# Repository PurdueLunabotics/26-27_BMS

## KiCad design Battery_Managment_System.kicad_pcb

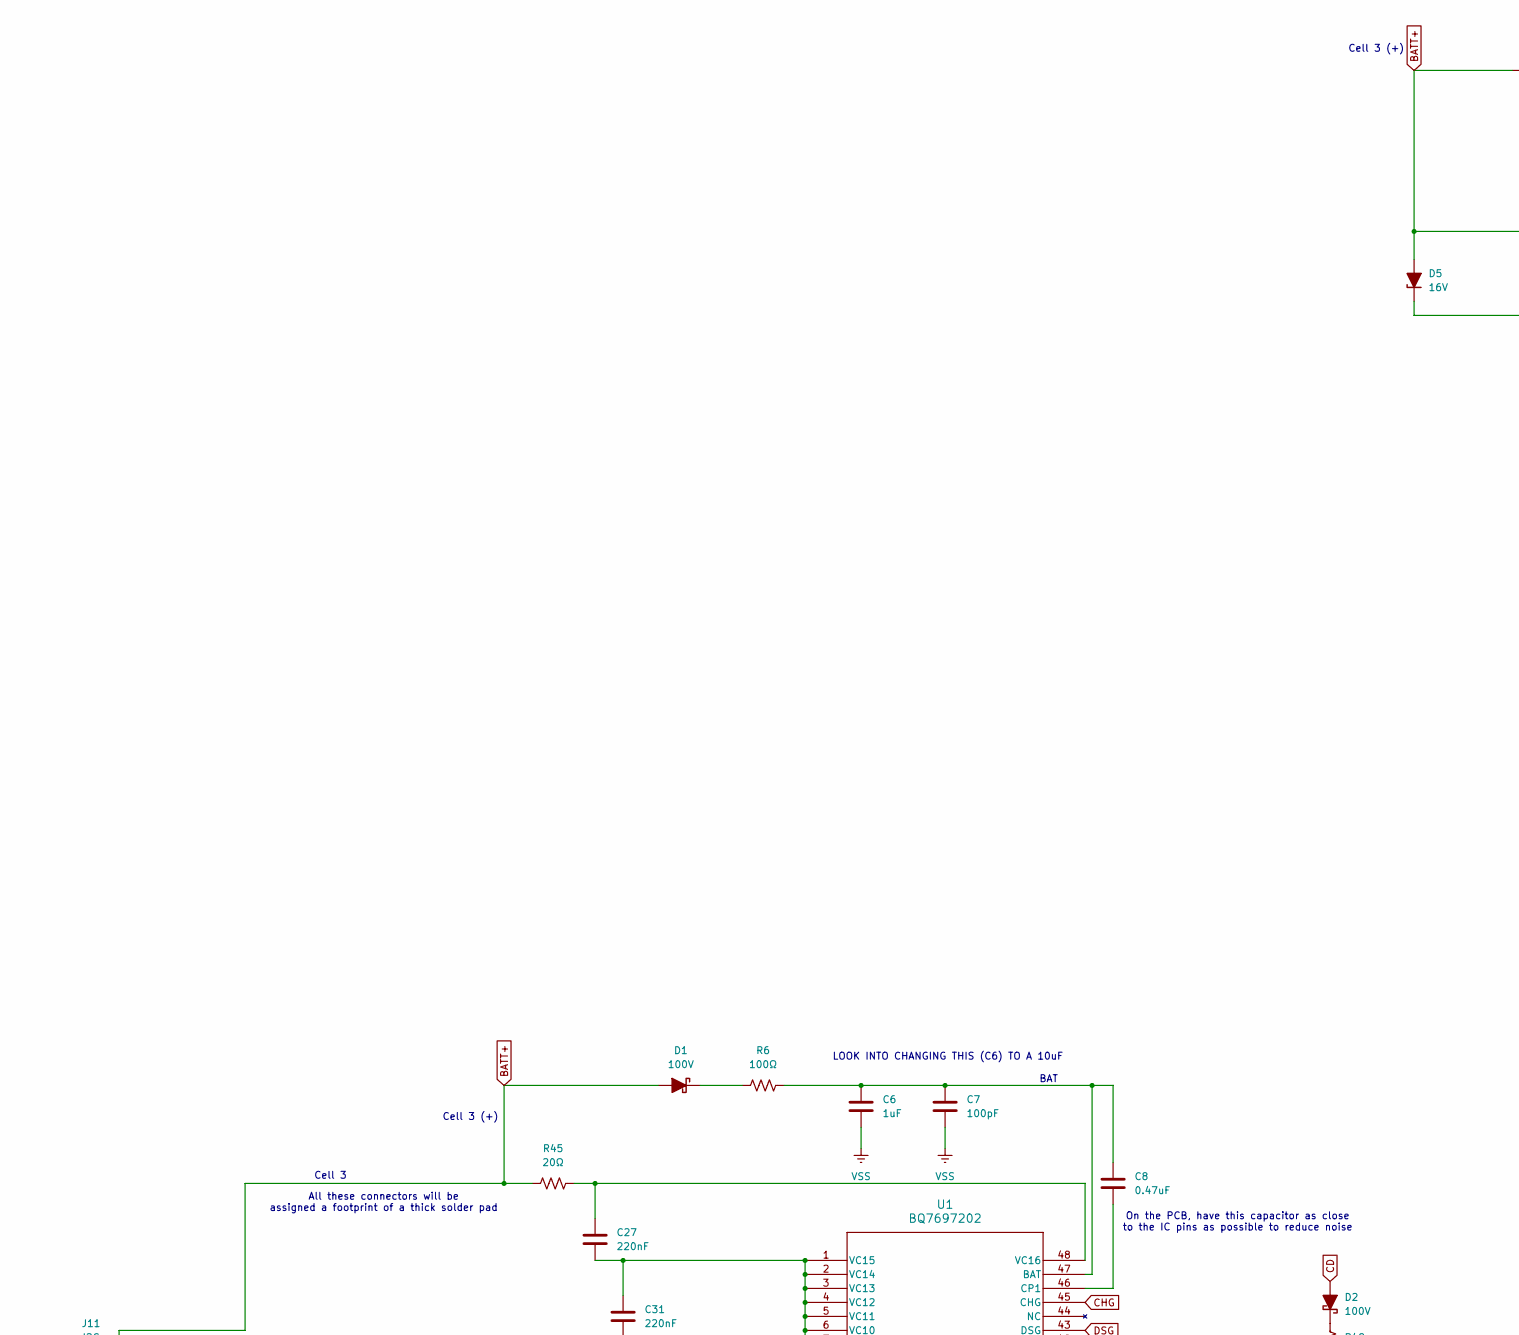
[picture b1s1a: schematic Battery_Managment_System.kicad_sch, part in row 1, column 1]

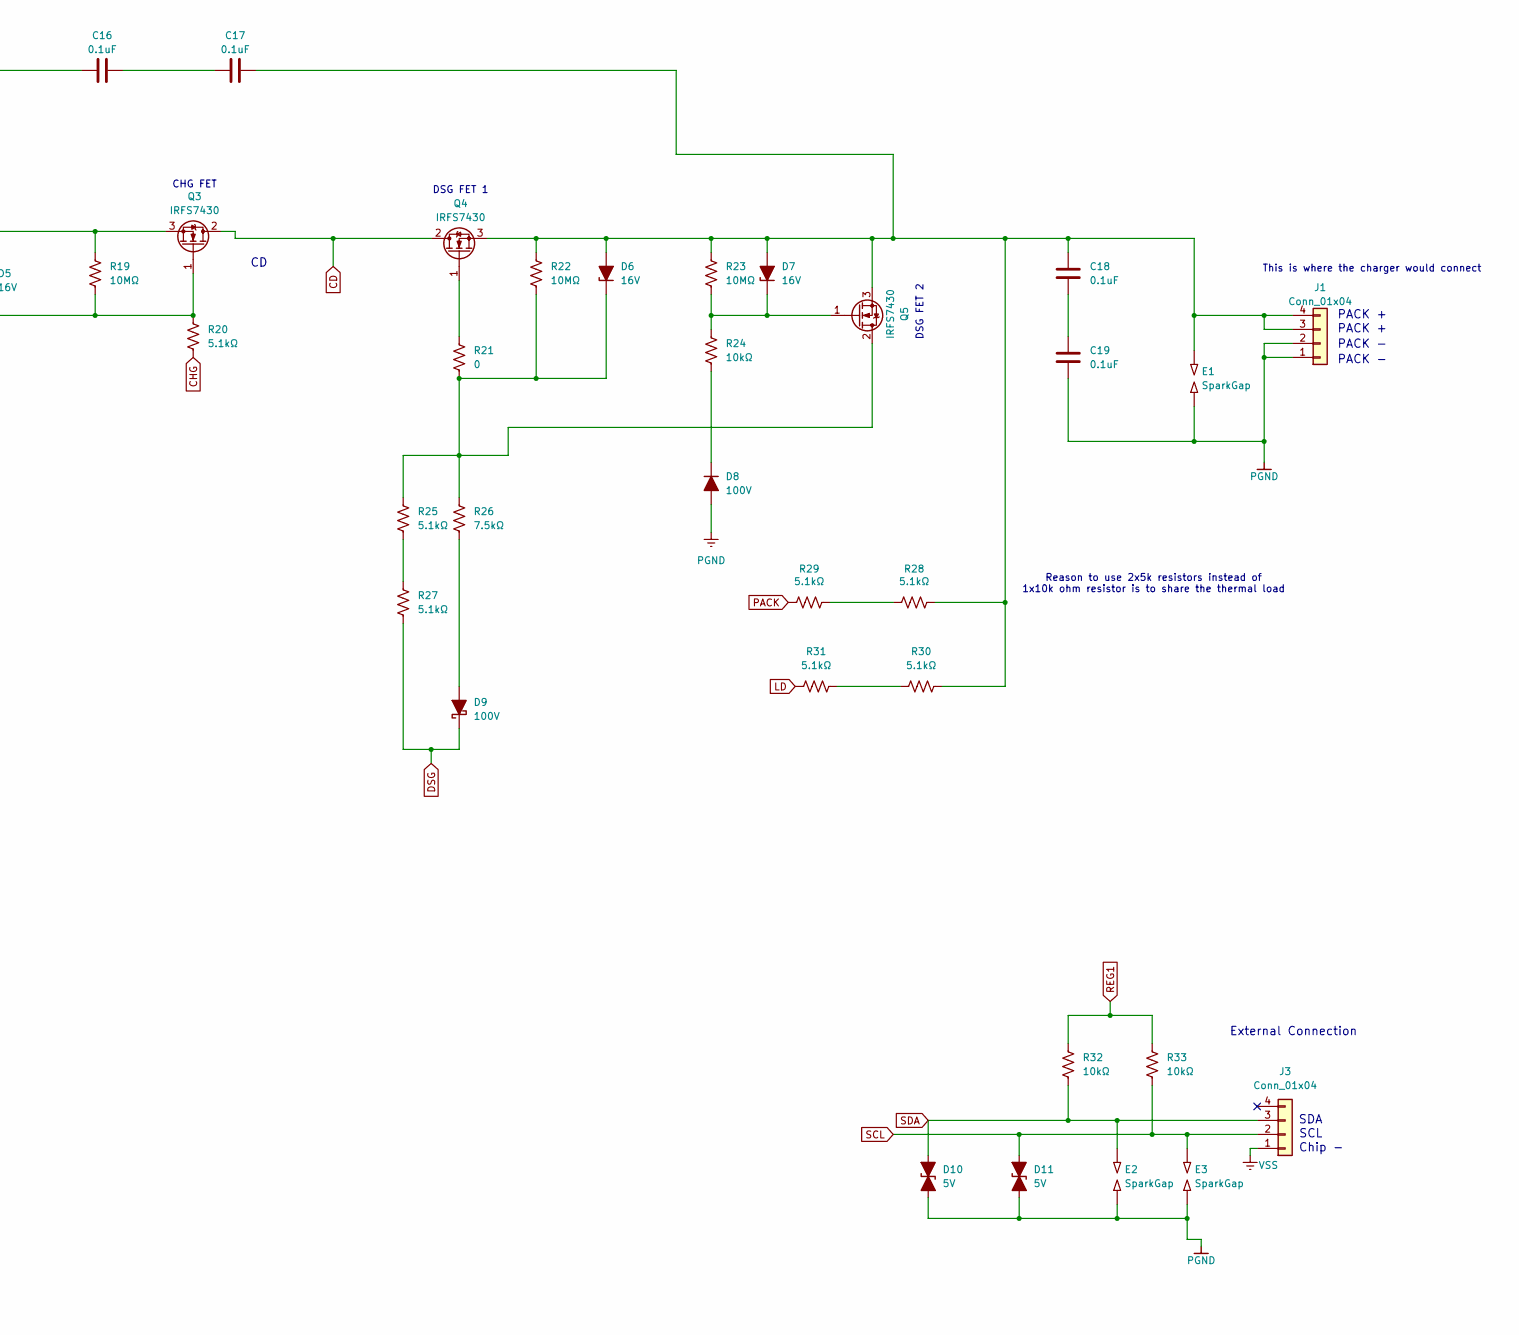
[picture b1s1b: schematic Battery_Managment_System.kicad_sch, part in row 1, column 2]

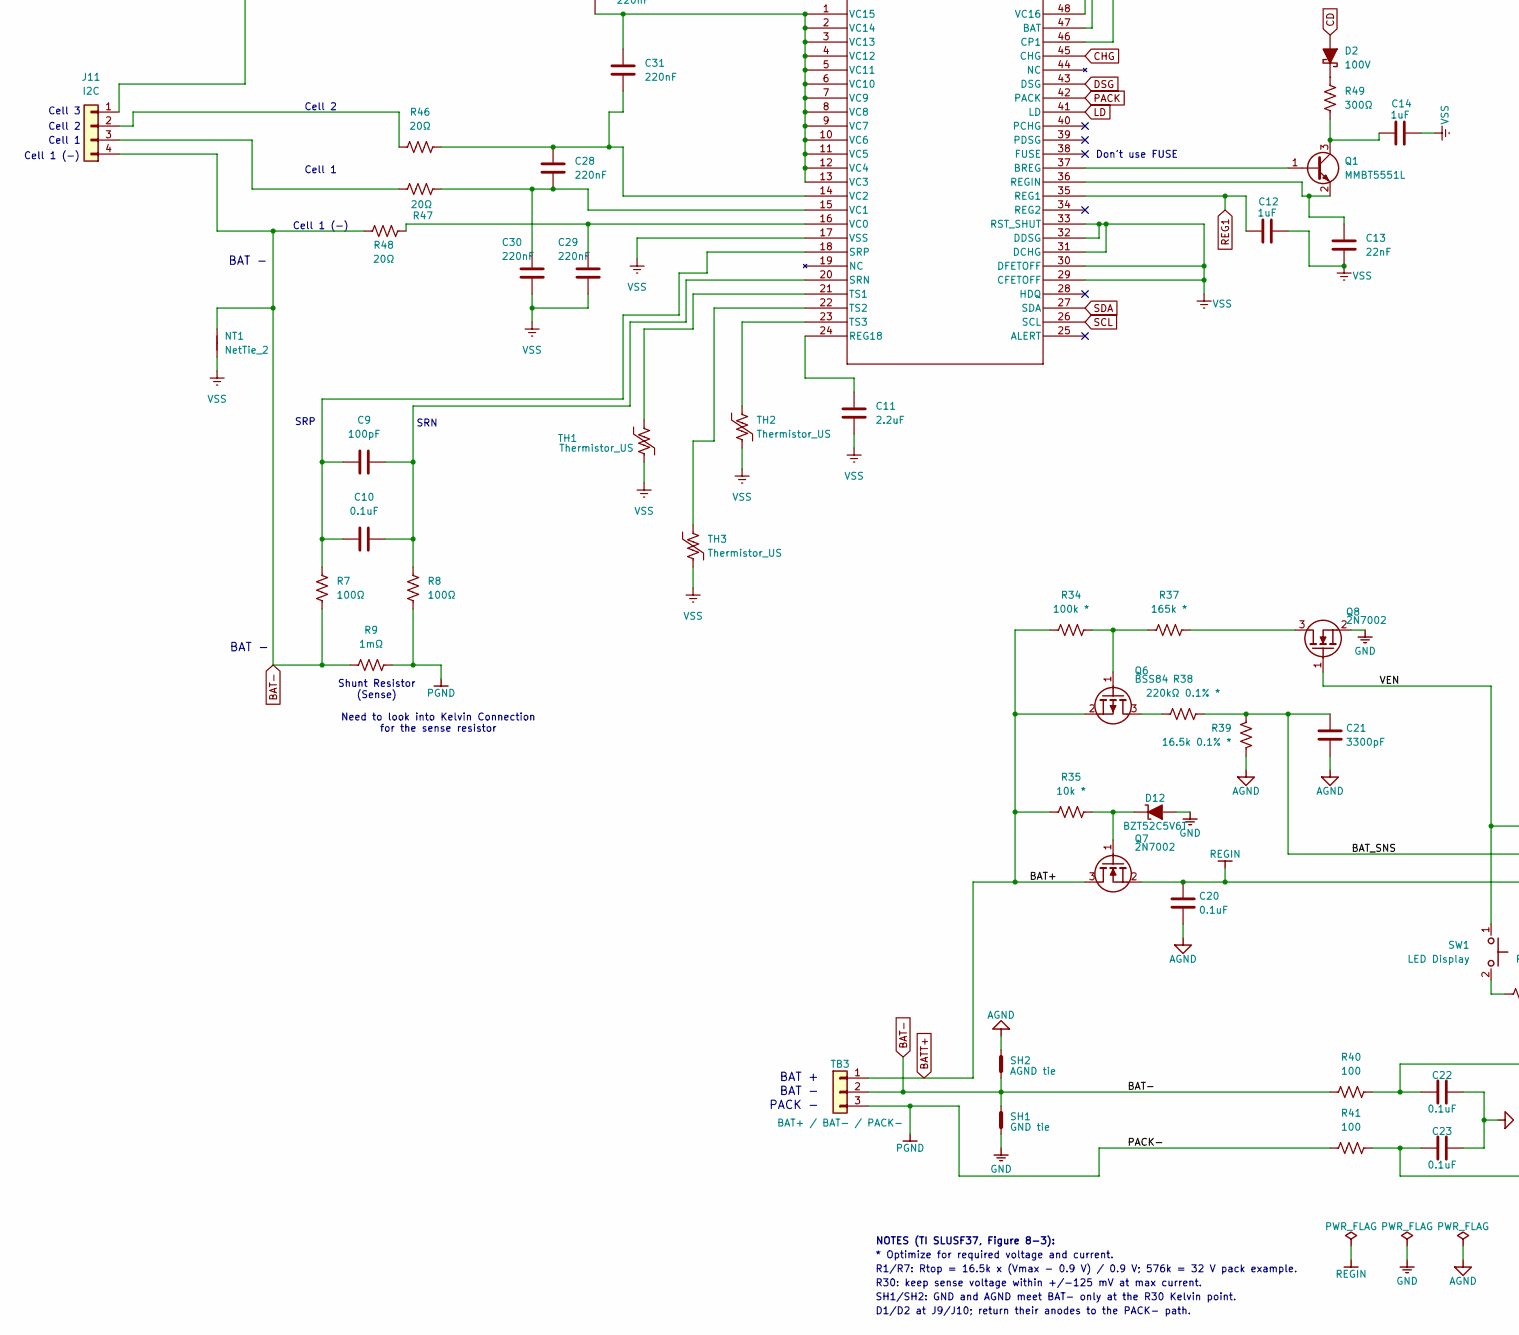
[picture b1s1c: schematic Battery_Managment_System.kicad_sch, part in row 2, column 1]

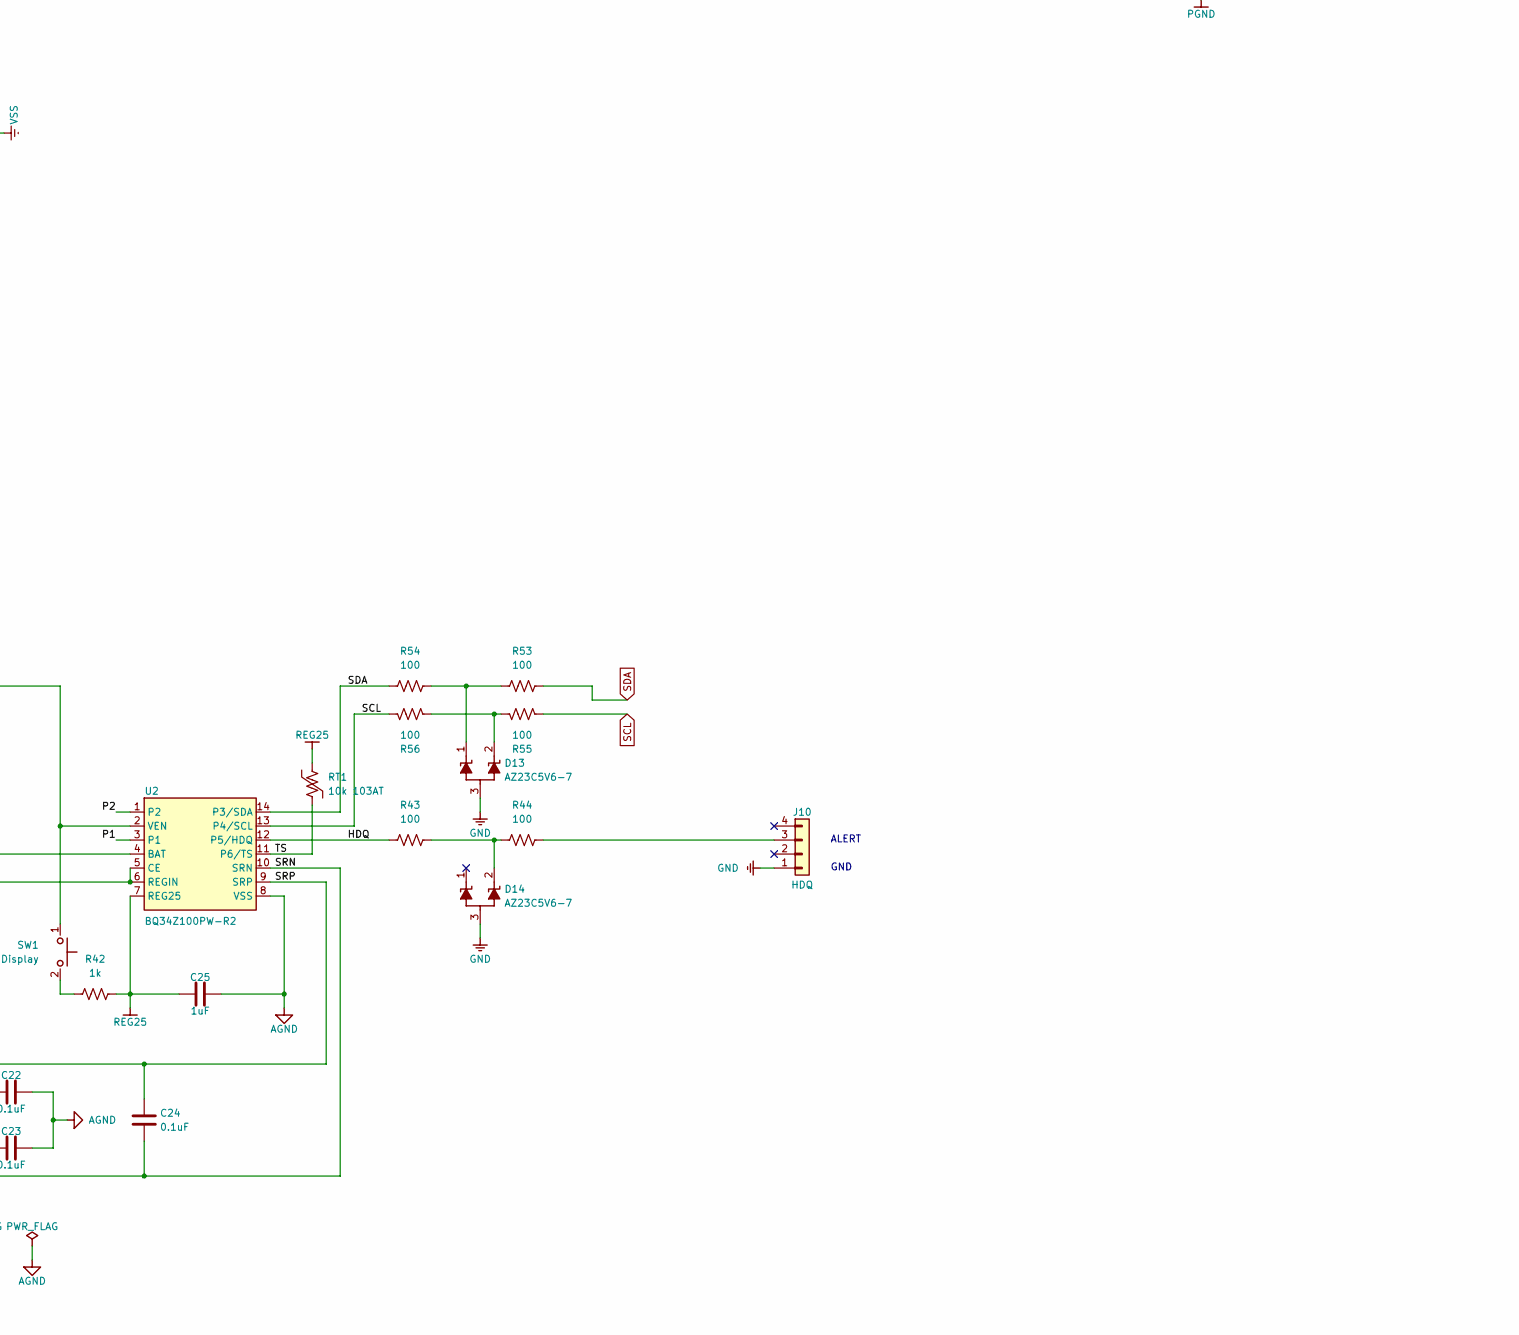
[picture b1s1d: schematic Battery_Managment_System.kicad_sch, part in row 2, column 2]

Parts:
C6, C12, C14: 1uF; C_0402_1005Metric
C7, C9: 100pF; C_0402_1005Metric
C8: 0.47uF; C_0402_1005Metric
C10, C16, C17, C18, C19, C22, C23, C24: 0.1uF; C_0402_1005Metric
C11: 2.2uF; C_0402_1005Metric
C13: 22nF; C_0402_1005Metric
C20: 0.1uF; C_0402_1005Metric; Voltage 16V
C21: 3300pF; C_0402_1005Metric
C25: 1uF; C_0402_1005Metric; Voltage 10V
C27, C28, C29, C30, C31: 220nF; C_0402_1005Metric
D1, D2, D8, D9: 100V; D_1210_3225Metric
D5, D6, D7: 16V; D_1210_3225Metric
D10, D11: 5V; D_1210_3225Metric
D12: BZT52C5V6T; D_SOD-523; MPN BZT52C5V6T-7
D13, D14: AZ23C5V6-7; SOT-23; MPN AZ23C5V6-7
E1, E2, E3: SparkGap; C_3640_9110Metric
J1, J3: Conn_01x04; Wago_734-134_1x04_P3.50mm_Vertical
J10: HDQ; Wago_734-134_1x04_P3.50mm_Vertical
J11: I2C; Wago_734-134_1x04_P3.50mm_Vertical
NT1: NetTie_2; SolderWire-1.5sqmm_1x01_D1.7mm_OD3.9mm
Q1: MMBT5551L; SOT-23
Q3, Q4, Q5: IRFS7430; TO-263-2
Q6: BSS84; SOT-23; MPN BSS84
Q7, Q8: 2N7002; SOT-23; MPN 2N7002
R6, R7, R8: 100Ω; R_0402_1005Metric
R9: 1mΩ; R_0402_1005Metric
R19, R22, R23: 10MΩ; R_0402_1005Metric
R20, R25, R27, R28, R29, R30, R31: 5.1kΩ; R_0402_1005Metric
R21: 0; R_0402_1005Metric
R24, R32, R33: 10kΩ; R_0402_1005Metric
R26: 7.5kΩ; R_0402_1005Metric
R34: 100k *; R_0402_1005Metric
R35: 10k *; R_0402_1005Metric
R37: 165k *; R_0402_1005Metric
R38: 220kΩ 0.1% *; R_1206_3216Metric; Tolerance 0.1% 25ppm
R39: 16.5k 0.1% *; R_0603_1608Metric; Tolerance 0.1% 25ppm
R40, R41, R43, R44: 100; R_0402_1005Metric
R42: 1k; R_0402_1005Metric
R45, R46, R47, R48: 20Ω; R_0402_1005Metric
R49: 300Ω; R_0402_1005Metric
R53, R54, R55, R56: 100; R_0603_1608Metric
RT1: 10k 103AT; PinHeader_1x02_P2.54mm_Vertical; MPN Semitec 103AT-2
SH1: GND tie; NetTie-2_SMD_Pad0.5mm
SH2: AGND tie; NetTie-2_SMD_Pad0.5mm
SW1: LED Display; SW_SPST_TL3342
TB3: BAT+ / BAT- / PACK-; TerminalBlock_Phoenix_MKDS-1,5-3_1x03_P5.00mm_Horizontal
TH1, TH2, TH3: Thermistor_US; JST_XH_B2B-XH-A_1x02_P2.50mm_Vertical
U1: BQ7697202; TQFP-48_7x7mm_P0.5mm
U2: BQ34Z100PW-R2; TSSOP-14_4.4x5mm_P0.65mm; MPN BQ34Z100PWR-R2

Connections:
/BAT_SNS: C21.1, R38.2, R39.1, U2.4 (BAT)
/HDQ: R43.1, U2.12 (P5/HDQ)
/P1: U2.3 (P1)
/P2: U2.1 (P2)
/SRN: C23.1, C24.2, R41.2, U2.10 (SRN)
/SRP: C22.1, C24.1, R40.2, U2.9 (SRP)
/TS: RT1.2, U2.11 (P6/TS)
/VEN: Q8.1 (G), SW1.1, U2.2 (VEN)
AGND: C20.2, C21.2, C22.2, C23.2, C25.2, R39.2, SH2.1, U2.8 (VSS)
BAT-: J11.4, NT1.2, R7.2, R9.1, R40.1, R48.2, SH1.1, SH2.2, TB3.2
BATT+: C16.1, D1.2 (A), D5.2 (A), J11.1, Q3.3 (S), Q6.2 (S), Q7.3 (D), R19.1, R34.1, R35.1, R45.1, TB3.1
CD: D2.2 (A), Q3.2 (D), Q4.2 (D)
CHG: R20.2, U1.45 (CHG)
DSG: D9.1 (K), R27.2, U1.43 (DSG)
GND: D12.2 (A), D13.3 (A), D14.3 (A), J10.1, Q8.2 (S), SH1.2
LD: R31.1, U1.41 (LD)
unnamed: C16.2, C17.1
unnamed: C18.2, C19.1
unnamed: D1.1 (K), R6.1
unnamed: D2.1 (K), R49.2
unnamed: D5.1 (K), Q3.1 (G), R19.2, R20.1
unnamed: C17.2, C18.1, D6.2 (A), D7.2 (A), E1.2, J1.3, J1.4, Q4.3 (S), Q5.3 (S), R22.1, R23.1, R28.2, R30.2
unnamed: D6.1 (K), Q5.2 (D), R21.2, R22.2, R25.1, R26.1
unnamed: D7.1 (K), Q5.1 (G), R23.2, R24.1
unnamed: D8.1 (K), R24.2
unnamed: D9.2 (A), R26.2
unnamed: D12.1 (K), Q7.1 (G), R35.2
unnamed: D13.1 (K1), R53.1, R54.2
unnamed: D13.2 (K2), R55.1, R56.2
unnamed: D14.2 (K2), R43.2, R44.1
unnamed: J10.3, R44.2
unnamed: J11.2, R46.1
unnamed: J11.3, R47.1
unnamed: Q1.1 (B), U1.37 (BREG)
unnamed: C14.1, Q1.3 (C), R49.1
unnamed: C13.1, Q1.2 (E), U1.36 (REGIN)
unnamed: Q4.1 (G), R21.1
unnamed: Q6.3 (D), R38.1
unnamed: Q6.1 (G), R34.2, R37.1
unnamed: Q8.3 (D), R37.2
unnamed: R25.2, R27.1
unnamed: R28.1, R29.2
unnamed: R30.1, R31.2
unnamed: R42.1, SW1.2
unnamed: C6.1, C7.1, C8.1, R6.2, U1.47 (BAT)
unnamed: C8.2, U1.46 (CP1)
unnamed: C11.1, U1.24 (REG18)
unnamed: C9.2, C10.2, R8.1, U1.20 (SRN)
unnamed: C9.1, C10.1, R7.1, U1.18 (SRP)
unnamed: TH1.1, U1.21 (TS1)
unnamed: TH3.1, U1.22 (TS2)
unnamed: TH2.1, U1.23 (TS3)
unnamed: C29.2, R48.1, U1.16 (VC0)
unnamed: C28.2, C30.2, R47.2, U1.15 (VC1)
unnamed: C28.1, C31.2, R46.2, U1.14 (VC2)
unnamed: C27.2, C31.1, U1.1 (VC15), U1.2 (VC14), U1.3 (VC13), U1.4 (VC12), U1.5 (VC11), U1.6 (VC10), U1.7 (VC9), U1.8 (VC8), U1.9 (VC7), U1.10 (VC6), U1.11 (VC5), U1.12 (VC4), U1.13 (VC3)
unnamed: C27.1, R45.2, U1.48 (VC16)
PACK: R29.1, U1.42 (PACK)
PGND: C19.2, D8.2 (A), D10.1 (A1), D11.1 (A1), E1.1, E2.1, E3.1, J1.1, J1.2, R8.2, R9.2, R41.1, TB3.3
REG1: C12.1, R32.1, R33.1, U1.35 (REG1)
REG25: C25.1, R42.2, RT1.1, U2.7 (REG25)
REGIN: C20.1, Q7.2 (S), U2.5 (CE), U2.6 (REGIN)
SCL: D11.2 (A2), E3.2, J3.2, R33.2, R55.2, R56.1, U1.26 (SCL), U2.13 (P4/SCL)
SDA: D10.2 (A2), E2.2, J3.3, R32.2, R53.2, R54.1, U1.27 (SDA), U2.14 (P3/SDA)
VSS: C6.2, C7.2, C11.2, C12.2, C13.2, C14.2, C29.1, C30.1, J3.1, NT1.1 (1_1), TH1.2, TH2.2, TH3.2, U1.17 (VSS), U1.29 (CFETOFF), U1.30 (DFETOFF), U1.31 (DCHG), U1.32 (DDSG), U1.33 (RST_SHUT)

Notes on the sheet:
Chip -
Reason to use 2x5k resistors instead of 1x10k ohm resistor is to share the thermal load
PACK -
SRP
R1/R7: Rtop = 16.5k x (Vmax - 0.9 V) / 0.9 V; 576k = 32 V pack example.
R30: keep sense voltage within +/-125 mV at max current.
GND
* Optimize for required voltage and current.
Cell 2
Need to look into Kelvin Connection for the sense resistor
DSG FET 1
BAT -
CHG FET
Cell 1
DSG FET 2
SRN
ALERT
Cell 1 (-)
Cell 3
External Connection
LOOK INTO CHANGING THIS (C6) TO A 10uF
Cell 3 (+)
PACK +
Shunt Resistor (Sense)
BAT
BAT +
SH1/SH2: GND and AGND meet BAT- only at the R30 Kelvin point.
D1/D2 at J9/J10; return their anodes to the PACK- path.
This is where the charger would connect
All these connectors will be assigned a footprint of a thick solder pad
On the PCB, have this capacitor as close to the IC pins as possible to reduce noise
SDA
Don't use FUSE
SCL
NOTES (TI SLUSF37, Figure 8-3):

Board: 2 copper layers, 99 parts (0 on the bottom side), 63 nets, no tracks yet.
